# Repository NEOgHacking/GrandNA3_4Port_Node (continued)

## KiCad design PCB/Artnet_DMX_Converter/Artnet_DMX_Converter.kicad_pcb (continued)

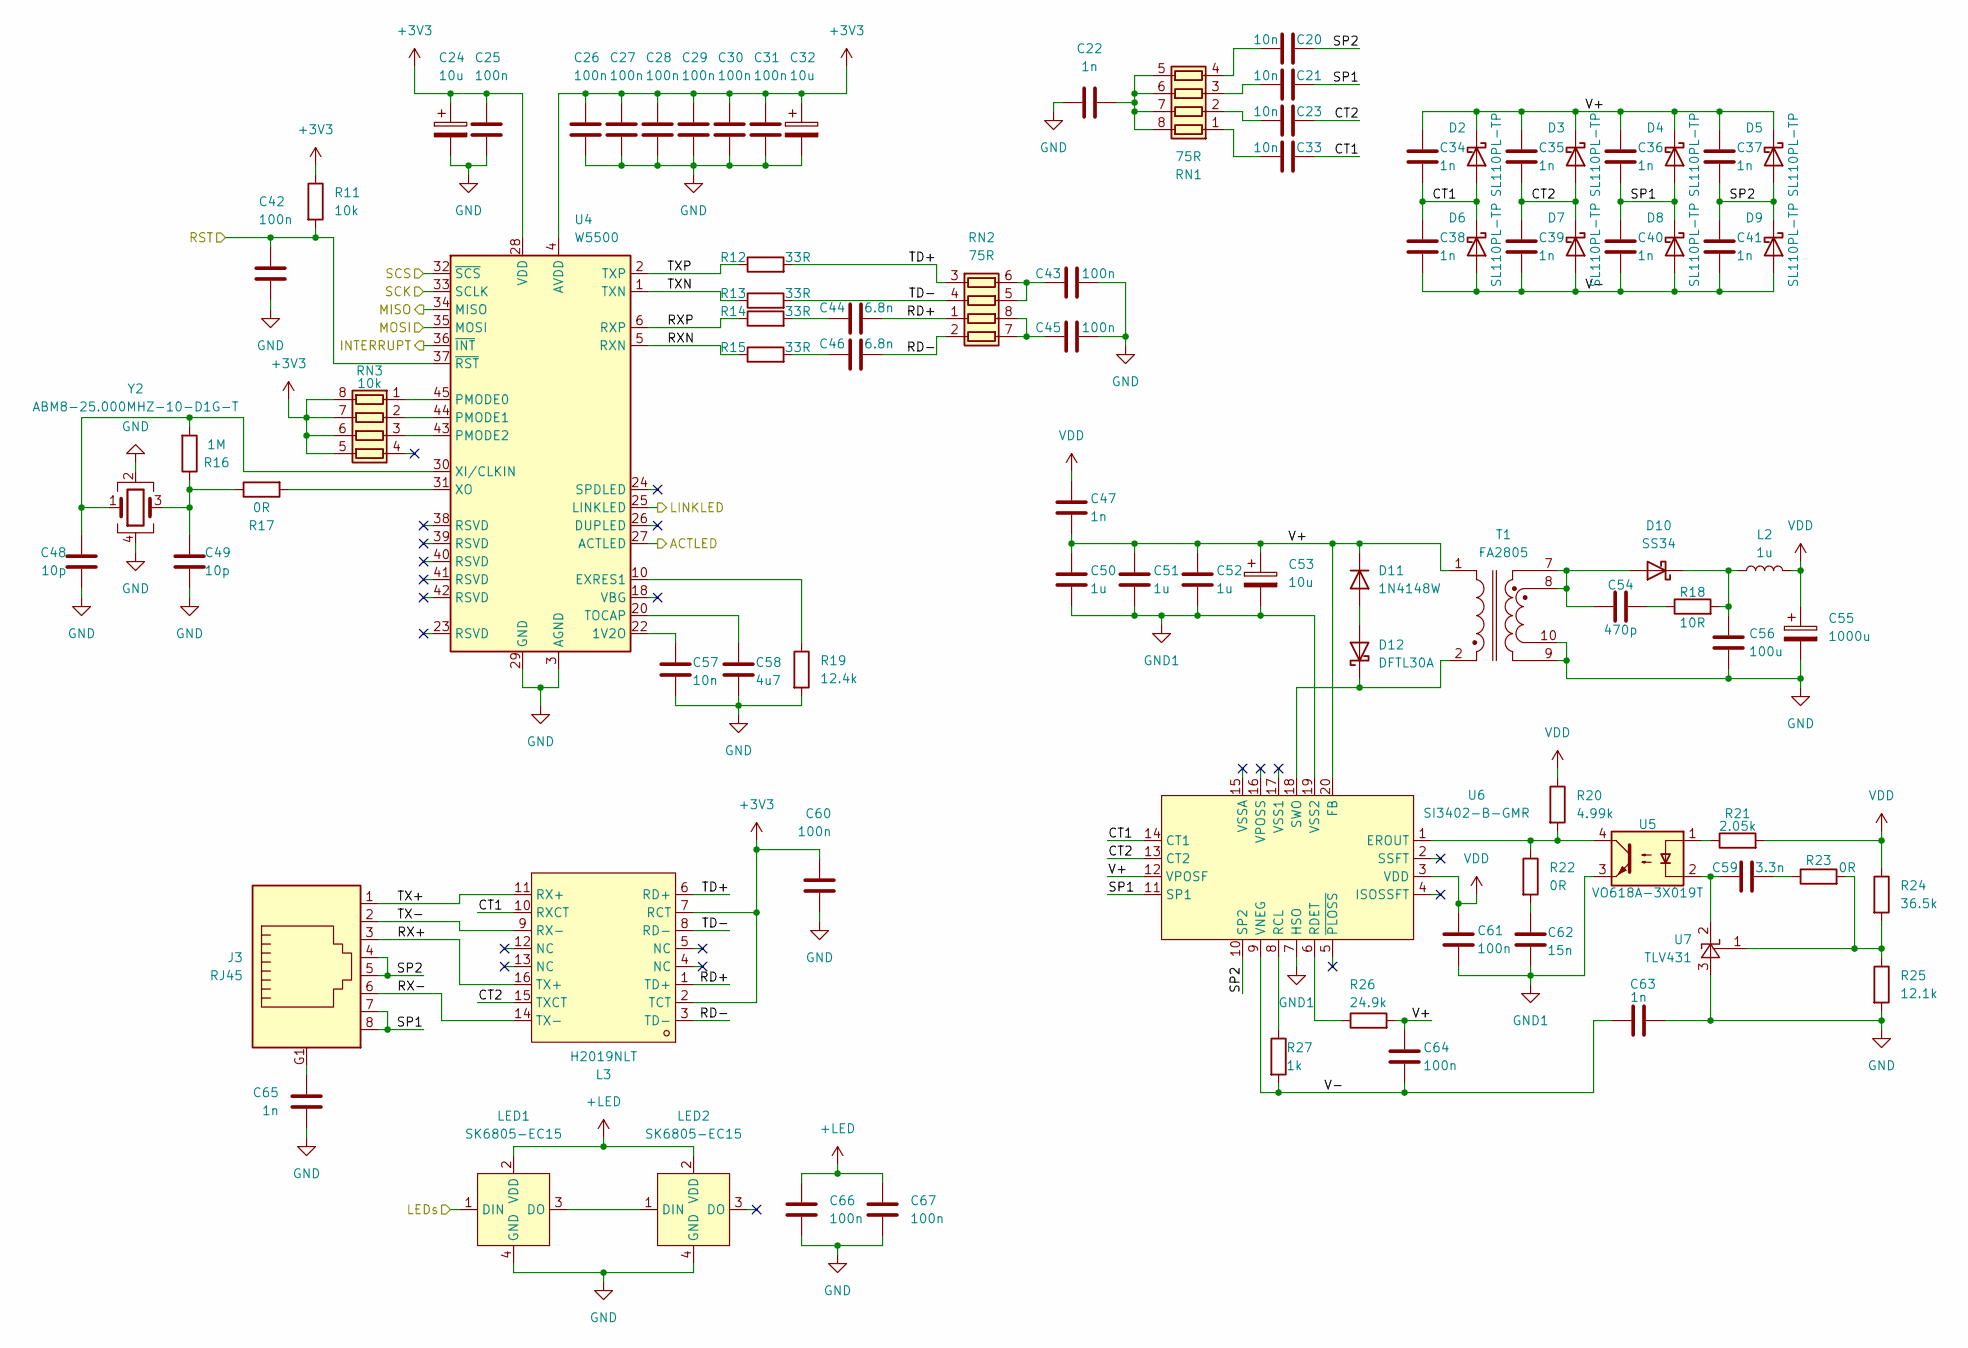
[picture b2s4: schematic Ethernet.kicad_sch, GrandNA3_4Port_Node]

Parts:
C20, C21, C23, C33, C57: 10n; C_0603_1608Metric
C22, C34, C35, C36, C37, C38, C39, C40, C41, C47, C63, C65: 1n; C_0603_1608Metric
C24, C32: 10u; CP_EIA-2012-12_Kemet-R
C25, C26, C27, C28, C29, C30, C31, C42, C43, C45, C60, C61, C64, C66, C67: 100n; C_0603_1608Metric
C44, C46: 6.8n; C_0603_1608Metric
C48, C49: 10p; C_0603_1608Metric
C50, C51, C52: 1u; C_0805_2012Metric
C53: 10u; CP_Elec_6.3x5.8
C54: 470p; C_0603_1608Metric
C55: 1000u; CP_Elec_10x10.5
C56: 100u; C_1206_3216Metric
C58: 4u7; C_0603_1608Metric
C59: 3.3n; C_0603_1608Metric
C62: 15n; C_0603_1608Metric
D2, D3, D4, D5, D6, D7, D8, D9: SL110PL-TP; D_SOD-123F
D10: SS34; D_SMA
D11: 1N4148W; D_SOD-123
D12: DFTL30A; D_SOD-123F
J3: RJ45; NE8FAHLRDAE
L2: 1u; L_Vishay_IHLP-1616
L3: H2019NLT; XFMR-SMD_16P-L12.7-W7.1-P1.27-LS9.4-BL; LCSC Part C110250
LED1, LED2: SK6805-EC15; LED-SMD_4P-L1.5-W1.5-BL; LCSC Part C2890035
R11: 10k; R_0603_1608Metric
R12, R13, R14, R15: 33R; R_0603_1608Metric
R16: 1M; R_0603_1608Metric
R17, R22, R23: 0R; R_0603_1608Metric
R18: 10R; R_0603_1608Metric
R19: 12.4k; R_0603_1608Metric
R20: 4.99k; R_0603_1608Metric
R21: 2.05k; R_0603_1608Metric
R24: 36.5k; R_0603_1608Metric
R25: 12.1k; R_0603_1608Metric
R26: 24.9k; R_0603_1608Metric
R27: 1k; R_0603_1608Metric
RN1, RN2: 75R; R_Array_Concave_4x0603
RN3: 10k; R_Array_Concave_4x0603
T1: FA2805; FA2924ALD
U4: W5500; LQFP-48_7x7mm_P0.5mm
U5: VO618A-3X019T; SMDIP-4_W9.53mm_Clearance8mm
U6: SI3402-B-GMR; QFN-20_L5.0-W5.0-P0.80-TL-EP2.8; LCSC Part C510771
U7: TLV431; TSOT-23
Y2: ABM8-25.000MHZ-10-D1G-T; Crystal_SMD_3225-4Pin_3.2x2.5mm

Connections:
+3V3: C24.1, C25.1, C26.1, C27.1, C28.1, C29.1, C30.1, C31.1, C32.1, C60.1, L3.2 (TCT), L3.7 (RCT), R11.1, RN3.5 (R4.2), RN3.6 (R3.2), RN3.7 (R2.2), RN3.8 (R1.2), U4.4 (AVDD), U4.8 (AVDD), U4.11 (AVDD), U4.15 (AVDD), U4.17 (AVDD), U4.21 (AVDD), U4.28 (VDD); also elsewhere on the board
+LED: C66.1, C67.1, LED1.2 (VDD), LED2.2 (VDD); also elsewhere on the board
/Ethernet/ACTLED: U4.27 (ACTLED); also elsewhere on the board
/Ethernet/CT1: C33.1, C34.2, C38.1, D2.2 (A), D6.1 (K), L3.10 (RXCT), U6.14 (CT1)
/Ethernet/CT2: C23.1, C35.2, C39.1, D3.2 (A), D7.1 (K), L3.15 (TXCT), U6.13 (CT2)
/Ethernet/INTERRUPT: U4.36 (~INT); also elsewhere on the board
/Ethernet/LINKLED: U4.25 (LINKLED); also elsewhere on the board
/Ethernet/MISO: U4.34 (MISO); also elsewhere on the board
/Ethernet/MOSI: U4.35 (MOSI); also elsewhere on the board
/Ethernet/RD+: C44.2, L3.1 (TD+), RN2.1 (R1.1)
/Ethernet/RD-: C46.2, L3.3 (TD-), RN2.2 (R2.1)
/Ethernet/RST: C42.1, R11.2, U4.37 (~RST); also elsewhere on the board
/Ethernet/RX+: J3.3, L3.16 (TX+)
/Ethernet/RX-: J3.6, L3.14 (TX-)
/Ethernet/RXN: R15.1, U4.5 (RXN)
/Ethernet/RXP: R14.1, U4.6 (RXP)
/Ethernet/SCK: U4.33 (SCLK); also elsewhere on the board
/Ethernet/SCS: U4.32 (~SCS); also elsewhere on the board
/Ethernet/SP1: C21.1, C36.2, C40.1, D4.2 (A), D8.1 (K), J3.7, J3.8, U6.11 (SP1)
/Ethernet/SP2: C20.1, C37.2, C41.1, D5.2 (A), D9.1 (K), J3.4, J3.5, U6.10 (SP2)
/Ethernet/TD+: L3.6 (RD+), R12.2, RN2.3 (R3.1)
/Ethernet/TD-: L3.8 (RD-), R13.2, RN2.4 (R4.1)
/Ethernet/TX+: J3.1, L3.11 (RX+)
/Ethernet/TX-: J3.2, L3.9 (RX-)
/Ethernet/TXN: R13.1, U4.1 (TXN)
/Ethernet/TXP: R12.1, U4.2 (TXP)
/Ethernet/V+: C34.1, C35.1, C36.1, C37.1, C47.2, C50.1, C51.1, C52.1, C53.1, C64.1, D2.1 (K), D3.1 (K), D4.1 (K), D5.1 (K), D11.1 (K), R26.2, T1.1, U6.12 (VPOSF), U6.20 (FB)
/Ethernet/V-: C38.2, C39.2, C40.2, C41.2, C63.1, C64.2, D6.2 (A), D7.2 (A), D8.2 (A), D9.2 (A), R27.2, U6.9 (VNEG), U6.21 (EP)
/LEDS_THRU: LED1.1 (DIN); also elsewhere on the board
GND: C22.2, C24.2, C25.2, C26.2, C27.2, C28.2, C29.2, C30.2, C31.2, C32.2, C42.2, C43.2, C45.2, C48.2, C49.2, C55.2, C56.2, C57.2, C58.2, C60.2, C63.2, C65.2, C66.2, C67.2, LED1.4 (GND), LED2.4 (GND), R19.2, R25.2, T1.9, T1.10, U4.3 (AGND), U4.9 (AGND), U4.14 (AGND), U4.16 (AGND), U4.19 (AGND), U4.29 (GND), U4.48 (AGND), U7.3 (A), Y2.2 (G), Y2.4 (G); also elsewhere on the board
GND1: C50.2, C51.2, C52.2, C53.2, C61.2, C62.2, U5.3, U6.7 (HSO), U6.19 (VSS2)
unnamed: C44.1, R14.2
unnamed: C46.1, R15.2
unnamed: C49.1, R16.1, R17.1, Y2.3
unnamed: C54.2, R18.1
unnamed: C59.2, R23.1
unnamed: C62.1, R22.2
unnamed: C65.1, J3.G1
unnamed: C54.1, D10.2 (A), T1.7, T1.8
unnamed: C56.1, D10.1 (K), L2.1, R18.2
unnamed: D11.2 (A), D12.2 (A)
unnamed: D12.1 (K), T1.2, U6.18 (SWO)
unnamed: LED1.3 (DO), LED2.1 (DIN)
unnamed: R21.1, U5.1
unnamed: C33.2, RN1.1 (R1.1)
unnamed: C22.1, RN1.5 (R4.2), RN1.6 (R3.2), RN1.7 (R2.2), RN1.8 (R1.2)
unnamed: C23.2, RN1.2 (R2.1)
unnamed: C21.2, RN1.3 (R3.1)
unnamed: C20.2, RN1.4 (R4.1)
unnamed: C45.1, RN2.7 (R2.2), RN2.8 (R1.2)
unnamed: C43.1, RN2.5 (R4.2), RN2.6 (R3.2)
unnamed: RN3.1 (R1.1), U4.45 (PMODE0)
unnamed: RN3.2 (R2.1), U4.44 (PMODE1)
unnamed: RN3.3 (R3.1), U4.43 (PMODE2)
unnamed: C57.1, U4.22 (1V2O)
unnamed: R19.1, U4.10 (EXRES1)
unnamed: C58.1, U4.20 (TOCAP)
unnamed: C48.1, R16.2, U4.30 (XI/CLKIN), Y2.1
unnamed: R17.2, U4.31 (XO)
unnamed: R20.2, R22.1, U5.4, U6.1 (EROUT)
unnamed: R27.1, U6.8 (RCL)
unnamed: R26.1, U6.6 (RDET)
unnamed: C59.1, U5.2, U7.2 (K)
unnamed: R23.2, R24.2, R25.1, U7.1 (Test)
VDD: C47.1, C55.1, C61.1, L2.2, R20.1, R21.2, R24.1, U6.3 (VDD); also elsewhere on the board

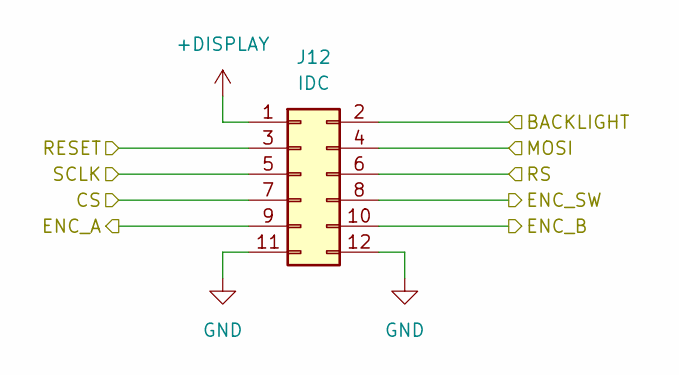
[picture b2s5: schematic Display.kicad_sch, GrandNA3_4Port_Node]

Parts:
J12: IDC; IDC-Header_2x06_P2.54mm_Vertical

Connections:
+DISPLAY: J12.1; also elsewhere on the board
/Display/BACKLIGHT: J12.2; also elsewhere on the board
/Display/CS: J12.7; also elsewhere on the board
/Display/ENC_A: J12.9; also elsewhere on the board
/Display/ENC_B: J12.10; also elsewhere on the board
/Display/ENC_SW: J12.8; also elsewhere on the board
/Display/MOSI: J12.4; also elsewhere on the board
/Display/RESET: J12.3; also elsewhere on the board
/Display/RS: J12.6; also elsewhere on the board
/Display/SCLK: J12.5; also elsewhere on the board
GND: J12.11, J12.12; also elsewhere on the board

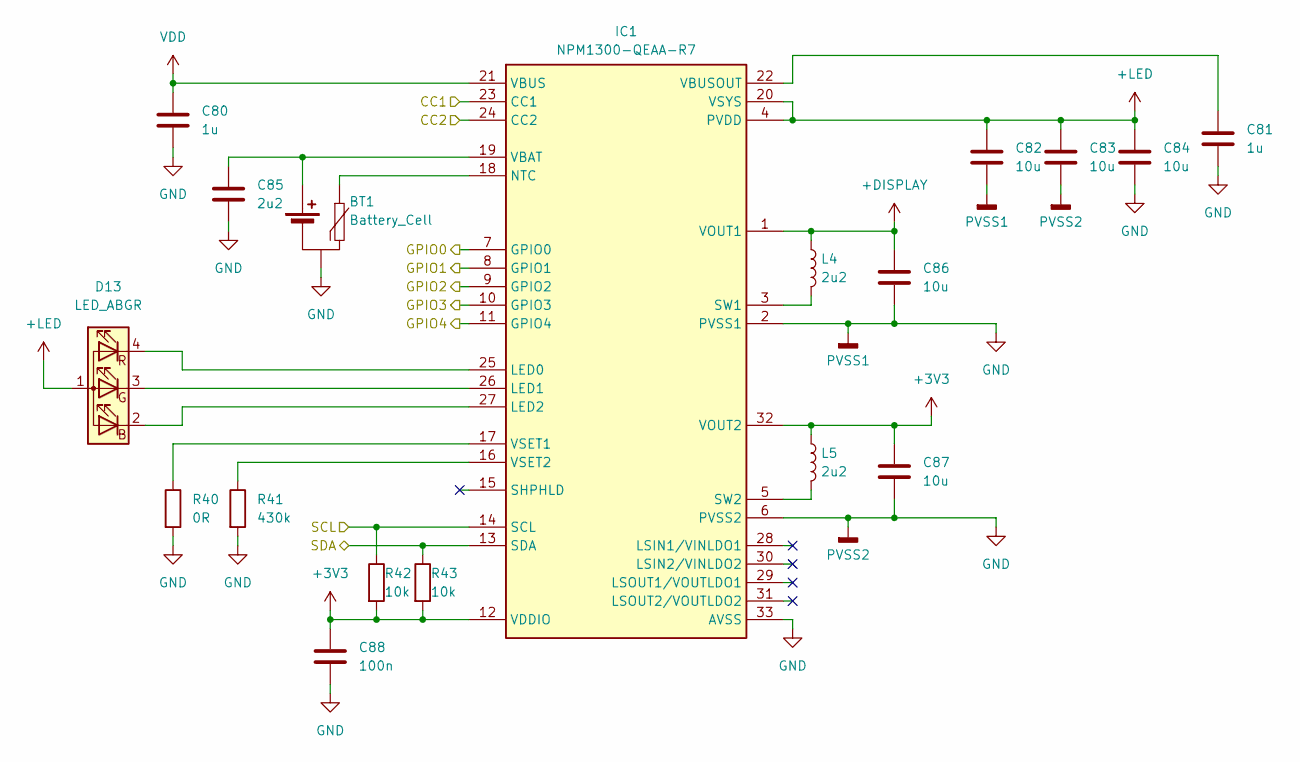
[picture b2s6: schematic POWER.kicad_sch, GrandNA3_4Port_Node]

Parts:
BT1: Battery_Cell; JST_XH_B3B-XH-A_1x03_P2.50mm_Vertical
C80, C81: 1u; C_0603_1608Metric
C82, C83, C84, C86, C87: 10u; C_0603_1608Metric
C85: 2u2; C_0603_1608Metric
C88: 100n; C_0603_1608Metric
D13: LED_ABGR; LED-SMD_4P-L1.6-W1.5-TR
IC1: NPM1300-QEAA-R7; QFN-32-1EP_5x5mm_P0.5mm_EP3.45x3.45mm_ThermalVias; Mouser Part Number 949-NPM1300-QEAA-R7
L4, L5: 2u2; L_0805_2012Metric
R40: 0R; R_0603_1608Metric
R41: 430k; R_0603_1608Metric
R42, R43: 10k; R_0603_1608Metric

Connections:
+3V3: C87.1, C88.1, IC1.12 (VDDIO), IC1.32 (VOUT2), L5.1, R42.2, R43.2; also elsewhere on the board
+DISPLAY: C86.1, IC1.1 (VOUT1), L4.1; also elsewhere on the board
+LED: C82.1, C83.1, C84.1, D13.1 (A), IC1.4 (PVDD), IC1.20 (VSYS); also elsewhere on the board
/Microcontroller/GPIO16: IC1.11 (GPIO4); also elsewhere on the board
/Microcontroller/GPIO17: IC1.10 (GPIO3); also elsewhere on the board
/Microcontroller/GPIO18: IC1.9 (GPIO2); also elsewhere on the board
/Microcontroller/GPIO19: IC1.8 (GPIO1); also elsewhere on the board
/Microcontroller/GPIO20: IC1.7 (GPIO0); also elsewhere on the board
/Microcontroller/GPIO22_I2C1_SDA: IC1.13 (SDA), R43.1; also elsewhere on the board
/Microcontroller/GPIO23_I2C_SCL: IC1.14 (SCL), R42.1; also elsewhere on the board
/POWER/CC1: IC1.23 (CC1); also elsewhere on the board
/POWER/CC2: IC1.24 (CC2); also elsewhere on the board
GND: BT1.2 (-), C80.2, C81.2, C82.2, C83.2, C84.2, C85.2, C86.2, C87.2, C88.2, IC1.2 (PVSS1), IC1.6 (PVSS2), IC1.33 (AVSS), R40.2, R41.2; also elsewhere on the board
unnamed: BT1.1 (+), C85.1, IC1.19 (VBAT)
unnamed: BT1.3 (NTC), IC1.18 (NTC)
unnamed: D13.2 (BK), IC1.27 (LED2)
unnamed: D13.3 (GK), IC1.26 (LED1)
unnamed: D13.4 (RK), IC1.25 (LED0)
unnamed: IC1.3 (SW1), L4.2
unnamed: IC1.5 (SW2), L5.2
unnamed: C81.1, IC1.22 (VBUSOUT)
unnamed: IC1.17 (VSET1), R40.1
unnamed: IC1.16 (VSET2), R41.1
VDD: C80.1, IC1.21 (VBUS); also elsewhere on the board

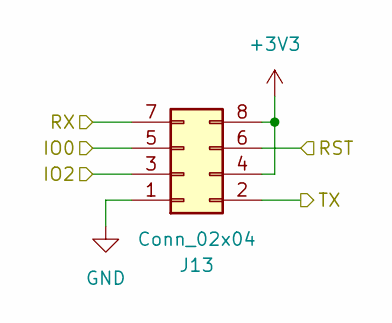
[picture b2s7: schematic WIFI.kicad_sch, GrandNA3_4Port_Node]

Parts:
J13: Conn_02x04; PinSocket_2x04_P2.54mm_Vertical

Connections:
+3V3: J13.4, J13.8; also elsewhere on the board
/Microcontroller/GPIO11: J13.3; also elsewhere on the board
/Microcontroller/GPIO12: J13.5; also elsewhere on the board
/Microcontroller/GPIO13: J13.6; also elsewhere on the board
/Microcontroller/GPIO14_UART1_TX: J13.7; also elsewhere on the board
/Microcontroller/GPIO15_UART1_RX: J13.2; also elsewhere on the board
GND: J13.1; also elsewhere on the board

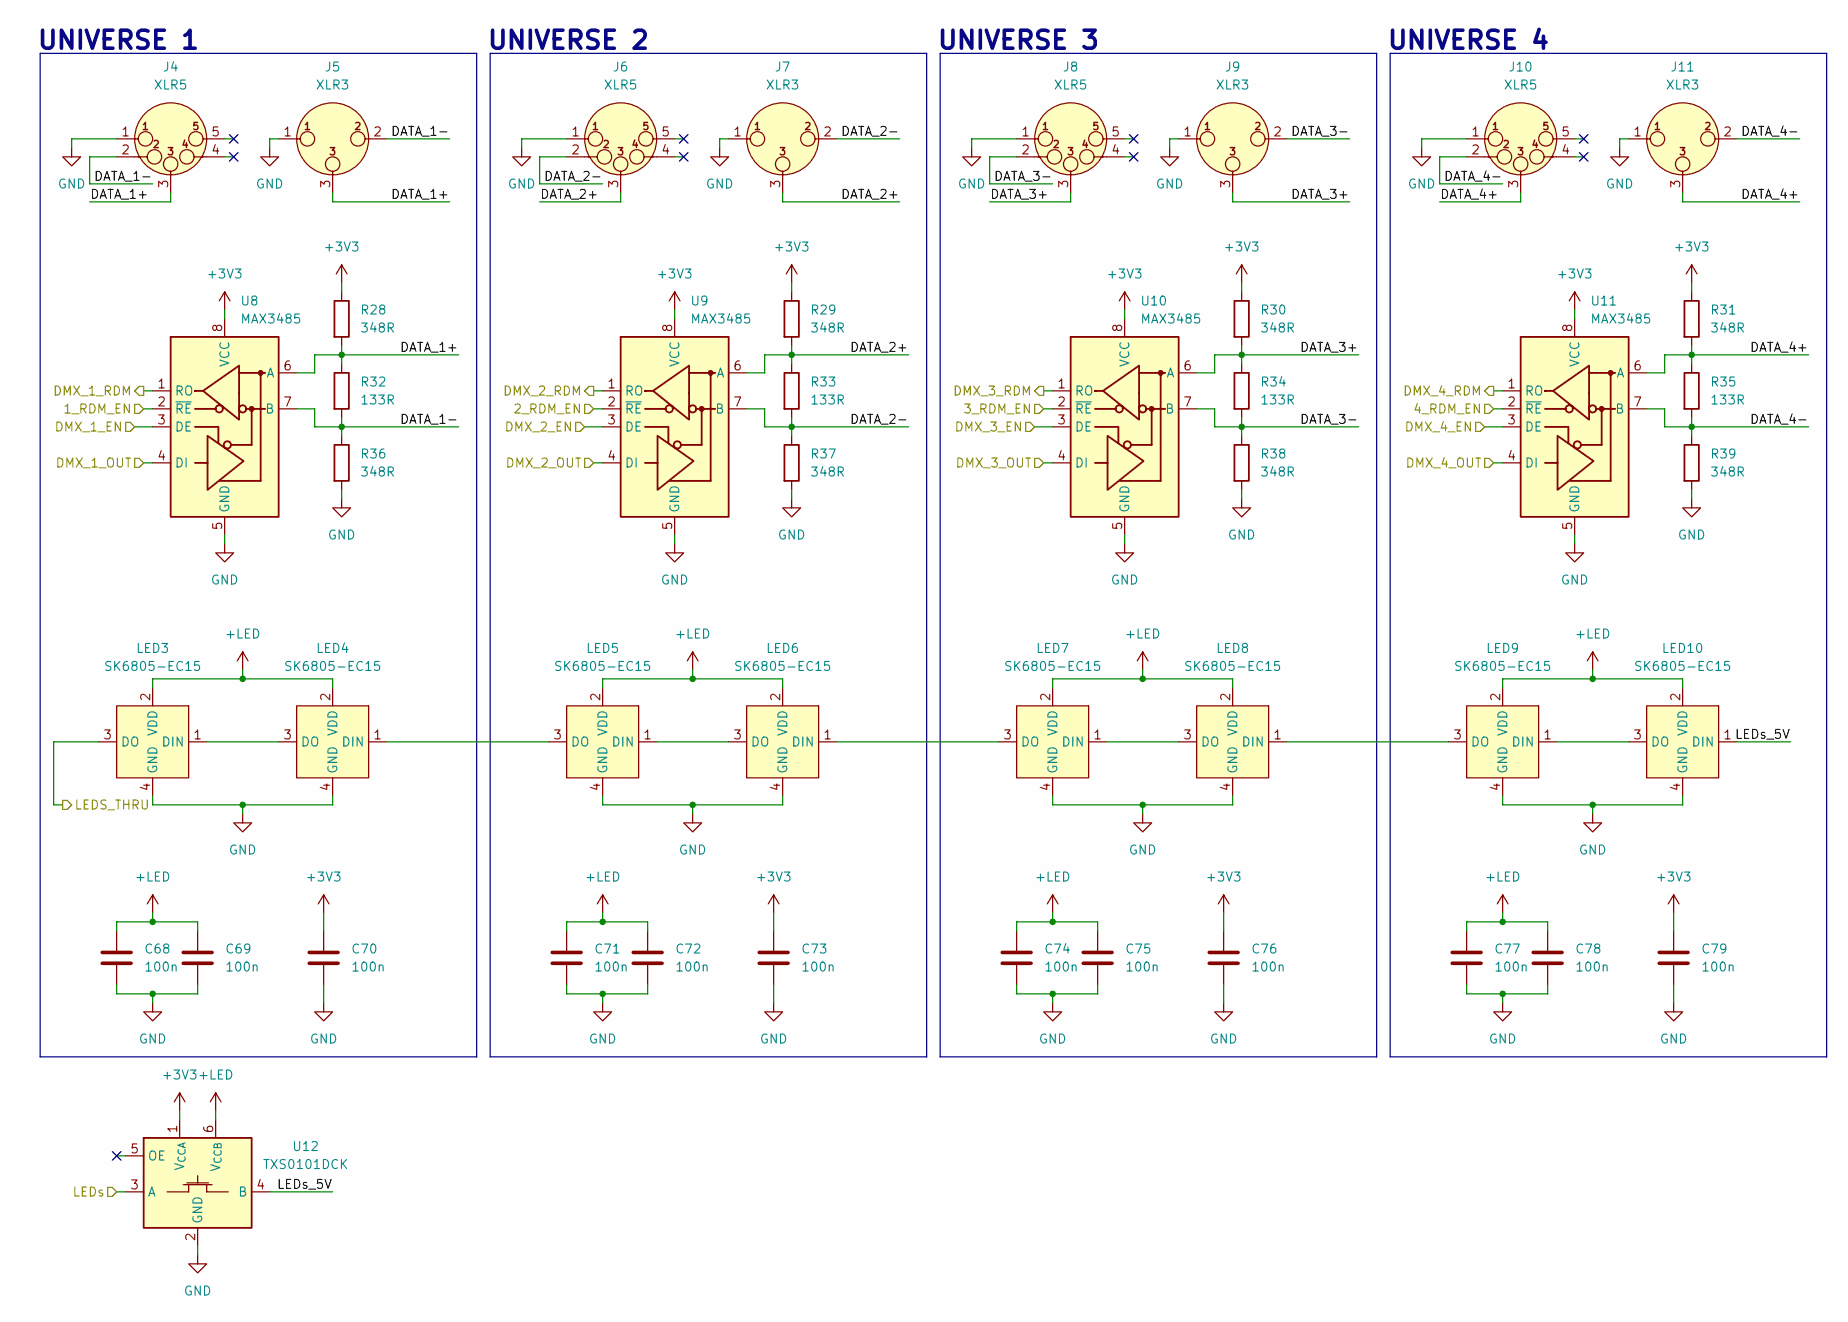
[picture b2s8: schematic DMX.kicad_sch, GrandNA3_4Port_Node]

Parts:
C68, C69, C70, C71, C72, C73, C74, C75, C76, C77, C78, C79: 100n; C_0603_1608Metric
J4, J6, J8, J10: XLR5; NC5FAH1-LR-DAE
J5, J7, J9, J11: XLR3; NC3FAH2-LR-DAE
LED3, LED4, LED5, LED6, LED7, LED8, LED9, LED10: SK6805-EC15; LED-SMD_4P-L1.5-W1.5-BL; LCSC Part C2890035
R28, R29, R30, R31, R36, R37, R38, R39: 348R; R_0603_1608Metric
R32, R33, R34, R35: 133R; R_0603_1608Metric
U8, U9, U10, U11: MAX3485; SOIC-8_3.9x4.9mm_P1.27mm
U12: TXS0101DCK; SOT-363_SC-70-6

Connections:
+3V3: C70.1, C73.1, C76.1, C79.1, R28.1, R29.1, R30.1, R31.1, U8.8 (VCC), U9.8 (VCC), U10.8 (VCC), U11.8 (VCC), U12.1 (V_{CCA}); also elsewhere on the board
+LED: C68.1, C69.1, C71.1, C72.1, C74.1, C75.1, C77.1, C78.1, LED3.2 (VDD), LED4.2 (VDD), LED5.2 (VDD), LED6.2 (VDD), LED7.2 (VDD), LED8.2 (VDD), LED9.2 (VDD), LED10.2 (VDD), U12.6 (V_{CCB}); also elsewhere on the board
/DMX/1_RDM_EN: U8.2 (~RE); also elsewhere on the board
/DMX/2_RDM_EN: U9.2 (~RE); also elsewhere on the board
/DMX/3_RDM_EN: U10.2 (~RE); also elsewhere on the board
/DMX/4_RDM_EN: U11.2 (~RE); also elsewhere on the board
/DMX/DATA_1+: J4.3, J5.3, R28.2, R32.1, U8.6 (A)
/DMX/DATA_1-: J4.2, J5.2, R32.2, R36.1, U8.7 (B)
/DMX/DATA_2+: J6.3, J7.3, R29.2, R33.1, U9.6 (A)
/DMX/DATA_2-: J6.2, J7.2, R33.2, R37.1, U9.7 (B)
/DMX/DATA_3+: J8.3, J9.3, R30.2, R34.1, U10.6 (A)
/DMX/DATA_3-: J8.2, J9.2, R34.2, R38.1, U10.7 (B)
/DMX/DATA_4+: J10.3, J11.3, R31.2, R35.1, U11.6 (A)
/DMX/DATA_4-: J10.2, J11.2, R35.2, R39.1, U11.7 (B)
/DMX/DMX_1_EN: U8.3 (DE); also elsewhere on the board
/DMX/DMX_1_OUT: U8.4 (DI); also elsewhere on the board
/DMX/DMX_1_RDM: U8.1 (RO); also elsewhere on the board
/DMX/DMX_2_EN: U9.3 (DE); also elsewhere on the board
/DMX/DMX_2_OUT: U9.4 (DI); also elsewhere on the board
/DMX/DMX_2_RDM: U9.1 (RO); also elsewhere on the board
/DMX/DMX_3_EN: U10.3 (DE); also elsewhere on the board
/DMX/DMX_3_OUT: U10.4 (DI); also elsewhere on the board
/DMX/DMX_3_RDM: U10.1 (RO); also elsewhere on the board
/DMX/DMX_4_EN: U11.3 (DE); also elsewhere on the board
/DMX/DMX_4_OUT: U11.4 (DI); also elsewhere on the board
/DMX/DMX_4_RDM: U11.1 (RO); also elsewhere on the board
/DMX/LEDs: U12.3 (A); also elsewhere on the board
/DMX/LEDs_5V: LED10.1 (DIN), U12.4 (B)
/LEDS_THRU: LED3.3 (DO); also elsewhere on the board
GND: C68.2, C69.2, C70.2, C71.2, C72.2, C73.2, C74.2, C75.2, C76.2, C77.2, C78.2, C79.2, J4.1, J5.1, J6.1, J7.1, J8.1, J9.1, J10.1, J11.1, LED3.4 (GND), LED4.4 (GND), LED5.4 (GND), LED6.4 (GND), LED7.4 (GND), LED8.4 (GND), LED9.4 (GND), LED10.4 (GND), R36.2, R37.2, R38.2, R39.2, U8.5 (GND), U9.5 (GND), U10.5 (GND), U11.5 (GND), U12.2 (GND); also elsewhere on the board
unnamed: LED3.1 (DIN), LED4.3 (DO)
unnamed: LED4.1 (DIN), LED5.3 (DO)
unnamed: LED5.1 (DIN), LED6.3 (DO)
unnamed: LED6.1 (DIN), LED7.3 (DO)
unnamed: LED7.1 (DIN), LED8.3 (DO)
unnamed: LED8.1 (DIN), LED9.3 (DO)
unnamed: LED9.1 (DIN), LED10.3 (DO)

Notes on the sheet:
UNIVERSE 1
UNIVERSE 3
UNIVERSE 4
UNIVERSE 2

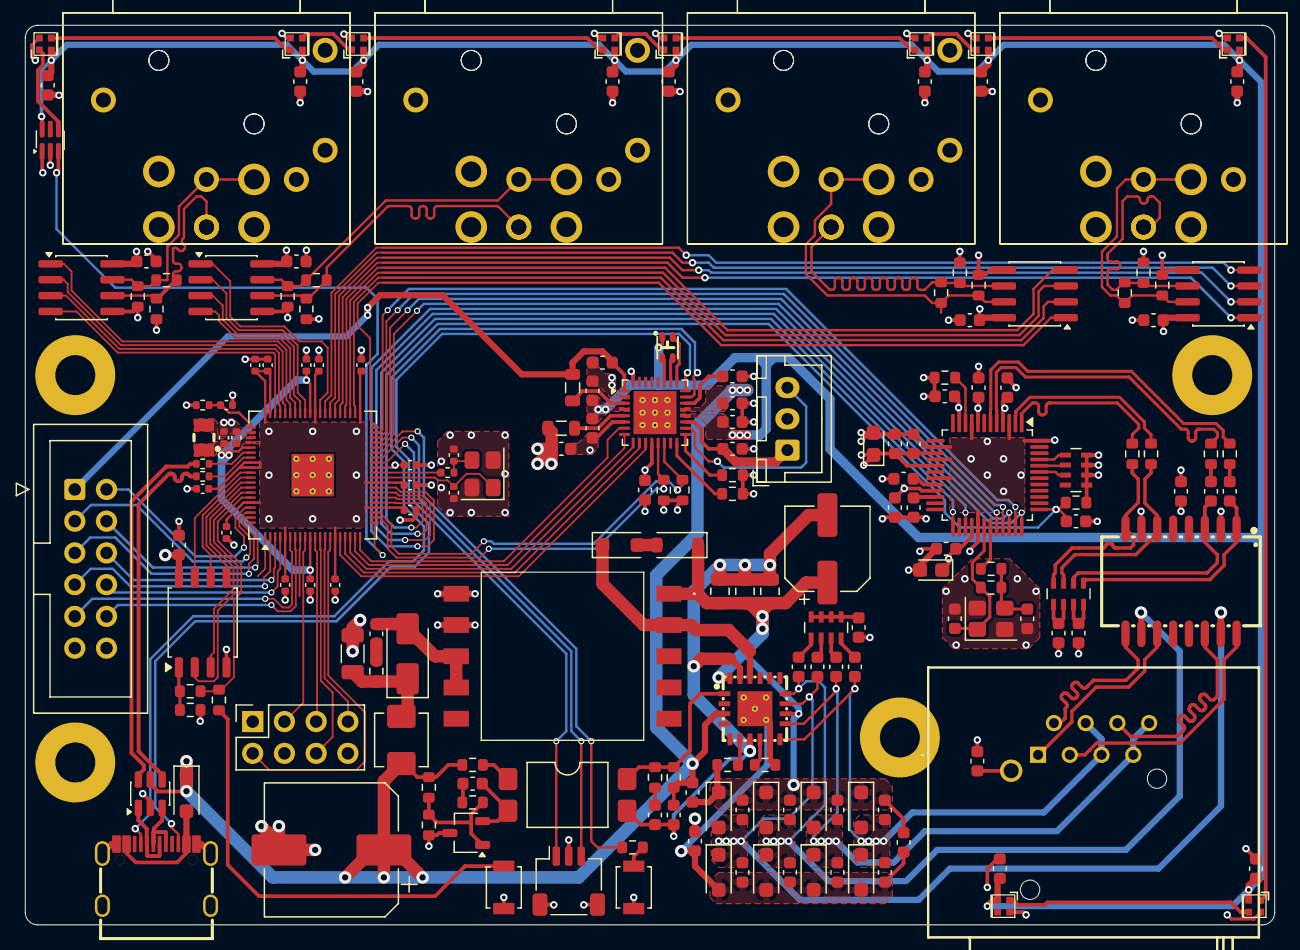
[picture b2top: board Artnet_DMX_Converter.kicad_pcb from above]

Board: 4 copper layers, 100.0 x 72.0 mm, 196 parts (0 on the bottom side), 157 nets.

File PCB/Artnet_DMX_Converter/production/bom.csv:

Designator,Footprint,Quantity,Value,LCSC Part #
BT1,JST_XH_B3B-XH-A_1x03_P2.50mm_Vertical,1,Battery_Cell,
"C1, C10, C11, C12, C13, C3, C4, C5, C6, C7, C8, C9",0402,12,100n,
"C14, C15, C16",0402,3,4.7u,
"C17, C19",0402,2,15p,
"C18, C25, C26, C27, C28, C29, C30, C31, C42, C43, C45, C60, C61, C64, C66, C67, C68, C69, C70, C71, C72, C73, C74, C75, C76, C77, C78, C79, C88",0603,29,100n,
C2,0402,1,4u7,
"C20, C21, C23, C33, C57",0603,5,10n,
"C22, C34, C35, C36, C37, C38, C39, C40, C41, C47, C63, C65",0603,12,1n,
"C24, C32",CP_EIA-2012-12_Kemet-R,2,10u,
"C44, C46",0603,2,6.8n,
"C48, C49",0603,2,10p,
"C50, C51, C52",0805,3,1u,
C53,CP_Elec_6.3x5.8,1,12u,
C54,0603,1,470p,
C55,CP_Elec_10x10.5,1,1000u,
C56,1206,1,100u,
C58,0603,1,4u7,
C59,0603,1,3.3n,
C62,0603,1,15n,
"C80, C81",0603,2,1u,
"C82, C83, C84, C86, C87",0603,5,10u,
C85,0603,1,2u2,
D1,D_SOD-123F,1,DSK24L,
D10,D_SMA,1,SS34,
D11,D_SOD-123,1,1N4148W,
D12,D_SOD-123F,1,DFTL30A,
D13,LED-SMD_4P-L1.6-W1.5-TR,1,LED_ABGR,
"D2, D3, D4, D5, D6, D7, D8, D9",D_SOD-123F,8,SL110PL-TP,
IC1,QFN-32-1EP_5x5mm_P0.5mm_EP3.45x3.45mm_ThermalVias,1,NPM1300-QEAA-R7,
J1,JST_SH_SM03B-SRSS-TB_1x03-1MP_P1.00mm_Horizontal,1,Conn_01x03_MountingPin,
"J10, J4, J6, J8",NC5FAH1-LR-DAE,4,XLR5,
"J11, J5, J7, J9",NC3FAH2-LR-DAE,4,XLR3,
J12,IDC-Header_2x06_P2.54mm_Vertical,1,IDC,
J13,PinSocket_2x04_P2.54mm_Vertical,1,Conn_02x04,
J2,USB-C_SMD-TYPE-C-31-M-12_1,1,USB_C_Receptacle_USB2.0_14P,
J3,NE8FAHLRDAE,1,RJ45,
L1,IND-SMD_L2.0-W1.6_AOTA-B201610S3R3-101-T,1,3.3u,
L2,L_Vishay_IHLP-1616,1,1u,
L3,XFMR-SMD_16P-L12.7-W7.1-P1.27-LS9.4-BL,1,H2019NLT,C110250
"L4, L5",0805,2,2u2,
"LED1, LED10, LED2, LED3, LED4, LED5, LED6, LED7, LED8, LED9",LED-SMD_4P-L1.5-W1.5-BL,10,SK6805-EC15,C2890035
"R1, R27, R3",0603,3,1k,
"R11, R42, R43, R7",0603,4,10k,
"R12, R13, R14, R15",0603,4,33R,
R16,0603,1,1M,
"R17, R22, R23, R8",0603,4,0R,
R18,0603,1,10R,
R19,0603,1,12.4k,
R2,0402,1,33R,
R20,0603,1,4.99k,
R21,0603,1,2.05k,
R24,0603,1,36.5k,
R25,0603,1,12.1k,
R26,0603,1,24.9k,
"R28, R29, R30, R31, R36, R37, R38, R39",0603,8,348R,
"R32, R33, R34, R35",0603,4,133R,
"R4, R5",0402,2,27R,
"R40, R41",0603,2,430k,
R6,0402,1,1k,
"RN1, RN2",R_Array_Concave_4x0603,2,75R,
RN3,R_Array_Concave_4x0603,1,10k,
"SW1, SW2",SW_SPST_B3U-1000P,2,SW_Push,
T1,FA2924ALD,1,FA2805,
U1,QFN-80-1EP_10x10mm_P0.4mm_EP3.4x3.4mm,1,RP2350B,
"U10, U11, U8, U9",SOIC-8_3.9x4.9mm_P1.27mm,4,MAX3485,
U12,SOT-363_SC-70-6,1,TXS0101DCK,
U2,SOIC-8_5.3x5.3mm_P1.27mm,1,W25Q128JVS,
U3,SOT-23-6,1,USBLC6-2SC6,
U4,LQFP-48_7x7mm_P0.5mm,1,W5500,
U5,SMDIP-4_W9.53mm_Clearance8mm,1,VO618A-3X019T,
U6,QFN-20_L5.0-W5.0-P0.80-TL-EP2.8,1,SI3402-B-GMR,C510771
U7,TSOT-23,1,TLV431,
Y1,Crystal_SMD_3225-4Pin_3.2x2.5mm,1,ABM8-272-T3,
Y2,Crystal_SMD_3225-4Pin_3.2x2.5mm,1,ABM8-25.000MHZ-10-D1G-T,

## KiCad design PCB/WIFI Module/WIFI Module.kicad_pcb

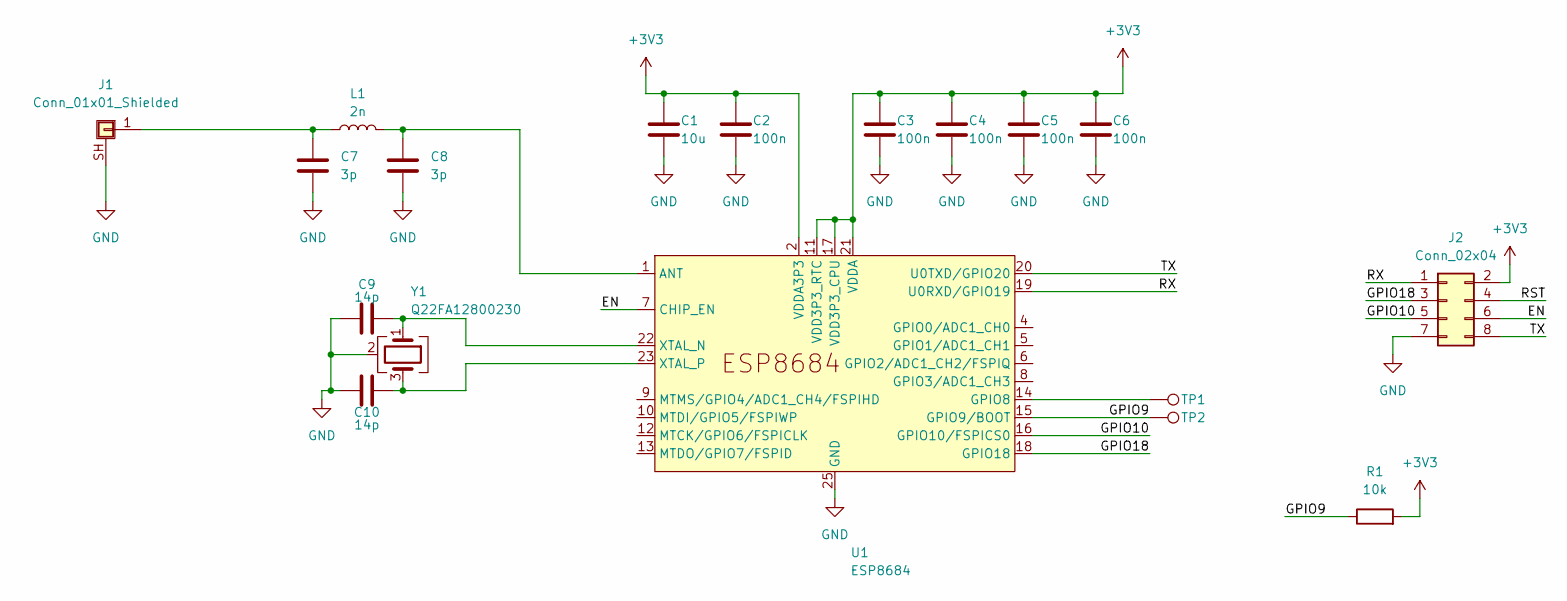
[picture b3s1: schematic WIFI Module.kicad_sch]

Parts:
C1: 10u; C_0603_1608Metric
C2, C3, C4, C5, C6: 100n; C_0402_1005Metric
C7, C8: 3p; C_0402_1005Metric
C9, C10: 14p; C_0402_1005Metric
J1: Conn_01x01_Shielded; U.FL_Molex_MCRF_73412-0110_Vertical
J2: Conn_02x04; PinHeader_2x04_P2.54mm_Vertical
L1: 2n; L_0402_1005Metric
R1: 10k; R_0402_1005Metric
TP1, TP2: TestPoint; TestPoint_Pad_D1.0mm
U1: ESP8684; QFN-24-1EP_4x4mm_P0.5mm_EP2.8x2.8mm
Y1: Q22FA12800230; Crystal_SMD_SeikoEpson_FA128-4Pin_2.0x1.6mm

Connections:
+3V3: C1.1, C2.1, C3.1, C4.1, C5.1, C6.1, J2.2, R1.2, U1.2 (VDDA3P3), U1.3 (VDDA3P3), U1.11 (VDD3P3_RTC), U1.17 (VDD3P3_CPU), U1.21 (VDDA), U1.24 (VDDA)
/EN: J2.6, U1.7 (CHIP_EN)
/GPIO9: R1.1, TP2.1, U1.15 (GPIO9/BOOT)
/GPIO10: J2.5, U1.16 (GPIO10/FSPICS0)
/GPIO18: J2.3, U1.18 (GPIO18)
/RST: J2.4
/RX: J2.1, U1.19 (U0RXD/GPIO19)
/TX: J2.8, U1.20 (U0TXD/GPIO20)
GND: C1.2, C2.2, C3.2, C4.2, C5.2, C6.2, C7.2, C8.2, C9.1, C10.1, J1.SH (Shield), J2.7, U1.25 (GND), Y1.2 (G), Y1.4 (G)
unnamed: C7.1, J1.1, L1.1
unnamed: C8.1, L1.2, U1.1 (ANT)
unnamed: TP1.1, U1.14 (GPIO8)
unnamed: C9.2, U1.22 (XTAL_N), Y1.1
unnamed: C10.2, U1.23 (XTAL_P), Y1.3

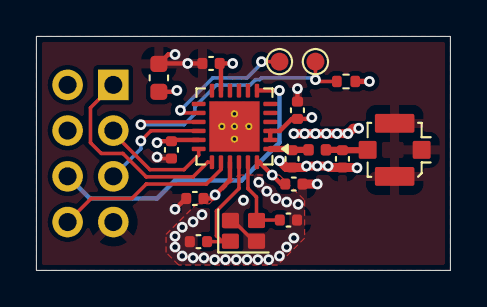
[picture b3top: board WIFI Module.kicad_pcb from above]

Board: 4 copper layers, 23.0 x 13.0 mm, 18 parts (1 on the bottom side), 13 nets.

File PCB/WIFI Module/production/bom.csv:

Designator,Footprint,Quantity,Value,LCSC Part #
C1,0603,1,10u,
"C10, C9",0402,2,14p,
"C2, C3, C4, C5, C6",0402,5,100n,
"C7, C8",0402,2,3p,
J1,U.FL_Molex_MCRF_73412-0110_Vertical,1,Conn_01x01_Shielded,
J2,PinHeader_2x04_P2.54mm_Vertical,1,Conn_02x04,
L1,0402,1,2n,
R1,0402,1,10k,
"TP1, TP2",TestPoint_Pad_D1.0mm,2,TestPoint,
U1,QFN-24-1EP_4x4mm_P0.5mm_EP2.8x2.8mm,1,ESP8684,
Y1,Crystal_SMD_SeikoEpson_FA128-4Pin_2.0x1.6mm,1,Q22FA12800230,

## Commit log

2026-02-22 Initial upload of PCB files ext.
2026-02-22 new bom
2026-02-22 Completed BOM and started renders
2026-02-23 Enhance README with detailed project description
    Expanded the README to provide detailed information about the GrandNA3_4Port_Node, including features, motivation, design process, and schematic references.
2026-02-23 Updated KiCad
2026-02-23 Updated pcb files again....
2026-02-26 Updated PCB files
2026-03-02 Added firmware and some changes to the PCB
2026-03-02 Updated blender with new renders
2026-03-02 Added pictures in the Assets folder
2026-03-02 Fix image paths for case images
    Updated image paths for case images in README.
2026-03-03 Fixed production files and added BOM.csv in BOMs folder and root folder
2026-03-03 Fixed some more stuff
2026-03-03 Added BOM
2026-03-03 Removed useless .obj
2026-03-03 Rename Display_PCB_schematic.png to Display_PCB_Schematic.png
2026-03-03 Include Onshape link in README
    Added Onshape link for the project case.
